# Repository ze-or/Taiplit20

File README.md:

# Taiplit20
20 key wireless split ergonomic keyboard

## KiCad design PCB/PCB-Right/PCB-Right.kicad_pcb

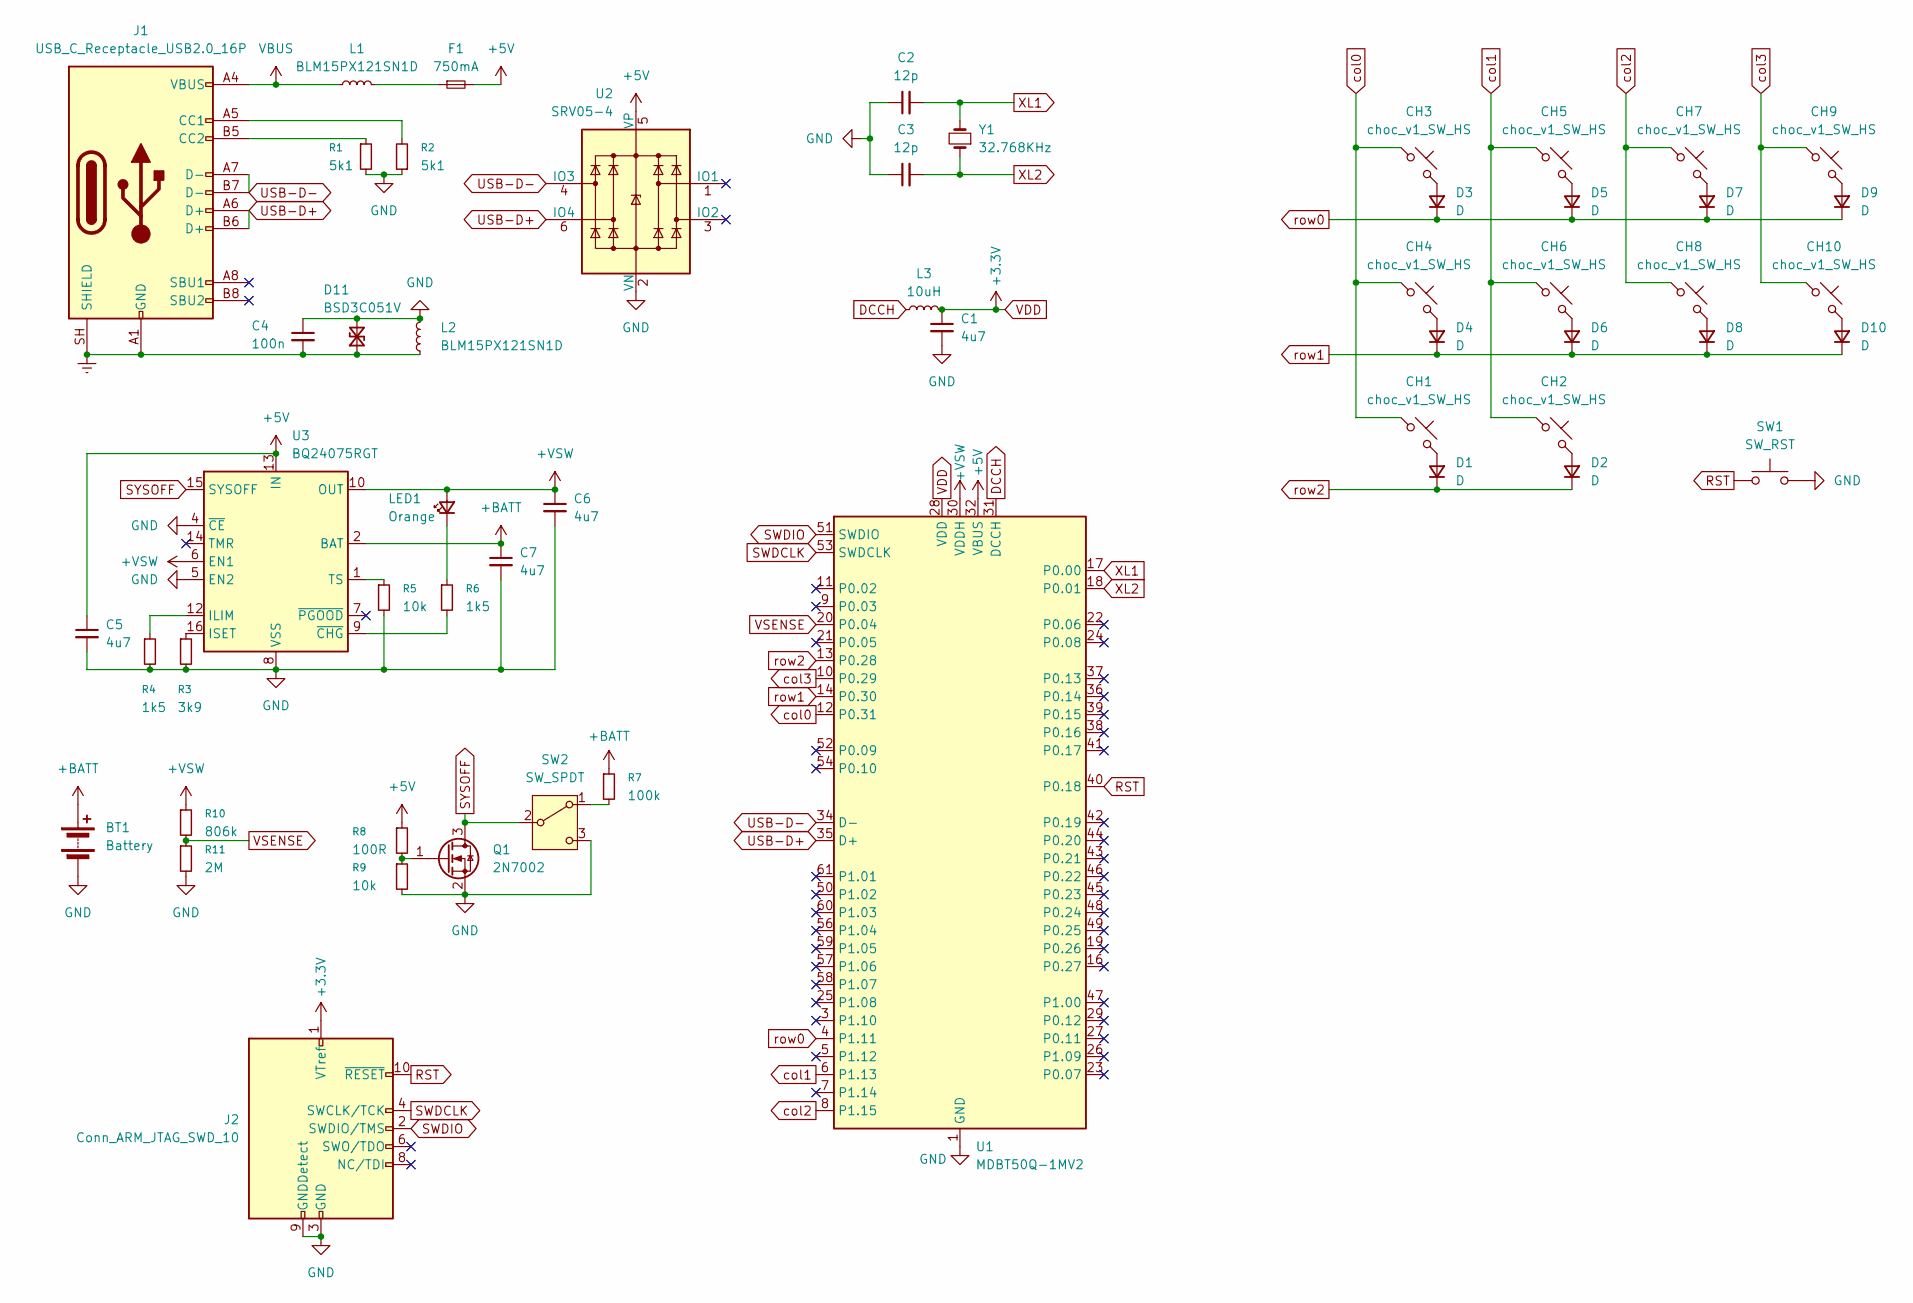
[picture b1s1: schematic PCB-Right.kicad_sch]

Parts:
BT1: Battery; JST_ACH_BM02B-ACHSS-GAN-ETF_1x02-1MP_P1.20mm_Vertical
C1, C5, C6, C7: 4u7; C_0603_1608Metric
C2, C3: 12p; C_0603_1608Metric
C4: 100n; C_0603_1608Metric
CH1, CH2, CH3, CH4, CH5, CH6, CH7, CH8, CH9, CH10: choc_v1_SW_HS; SW_choc_v2_HS_CPG135001S30_1u
D1, D2, D3, D4, D5, D6, D7, D8, D9, D10: D; D_SOD-123
D11: BSD3C051V; D_SOD-323
F1: 750mA; Fuse_1206_3216Metric
J1: USB_C_Receptacle_USB2.0_16P; USB_C_Receptacle_HRO_TYPE-C-31-M-12
J2: Conn_ARM_JTAG_SWD_10; PinHeader_2x05_P1.27mm_Vertical
L1, L2: BLM15PX121SN1D; L_0402_1005Metric
L3: 10uH; L_0603_1608Metric
LED1: Orange; LED_0805_2012Metric
Q1: 2N7002; SOT-23
R1, R2: 5k1; R_0603_1608Metric
R3: 3k9; R_0603_1608Metric
R4, R6: 1k5; R_0603_1608Metric
R5, R9: 10k; R_0603_1608Metric
R7: 100k; R_0603_1608Metric
R8: 100R; R_0603_1608Metric
R10: 806k; R_0603_1608Metric
R11: 2M; R_0603_1608Metric
SW1: SW_RST; SW_SPST_TL3342
SW2: SW_SPDT; SW_MSK12C02-HB
U1: MDBT50Q-1MV2; Raytac_MDBT50Q
U2: SRV05-4; SOT-23-6
U3: BQ24075RGT; VQFN-16-1EP_3x3mm_P0.5mm_EP1.6x1.6mm
Y1: 32.768KHz; Crystal_SMD_3215-2Pin_3.2x1.5mm

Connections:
+5V: C5.1, F1.2, R8.1, U1.32 (VBUS), U2.5 (VP), U3.13 (IN)
+BATT: BT1.1 (+), C7.1, R7.1, U3.2 (BAT), U3.3 (BAT)
+VSW: C6.1, LED1.2 (A), R10.1, U1.30 (VDDH), U3.6 (EN1), U3.10 (OUT), U3.11 (OUT)
DCCH: L3.1, U1.31 (DCCH)
Earth: C4.2, D11.1 (A1), J1.A1 (GND), J1.A12 (GND), J1.B1 (GND), J1.B12 (GND), J1.SH (SHIELD), L2.1
GND: BT1.2 (-), C1.2, C2.1, C3.1, C4.1, C5.2, C6.2, C7.2, D11.2 (A2), J2.3 (GND), J2.5 (GND), J2.9 (GNDDetect), L2.2, Q1.2 (S), R1.2, R2.1, R3.2, R4.2, R5.2, R9.2, R11.2, SW1.2, SW2.3 (C), U1.1 (GND), U1.2 (GND), U1.15 (GND), U1.33 (GND), U1.55 (GND), U2.2 (VN), U3.4 (~CE), U3.5 (EN2), U3.8 (VSS), U3.17 (VSS)
unnamed: CH1.2, D1.2 (A)
unnamed: CH2.2, D2.2 (A)
unnamed: CH3.2, D3.2 (A)
unnamed: CH4.2, D4.2 (A)
unnamed: CH5.2, D5.2 (A)
unnamed: CH6.2, D6.2 (A)
unnamed: CH7.2, D7.2 (A)
unnamed: CH8.2, D8.2 (A)
unnamed: CH9.2, D9.2 (A)
unnamed: CH10.2, D10.2 (A)
unnamed: F1.1, L1.2
unnamed: J1.A5 (CC1), R2.2
unnamed: J1.B5 (CC2), R1.1
unnamed: LED1.1 (K), R6.1
unnamed: Q1.1 (G), R8.2, R9.1
unnamed: R7.2, SW2.1 (A)
unnamed: R4.1, U3.12 (ILIM)
unnamed: R3.1, U3.16 (ISET)
unnamed: R5.1, U3.1 (TS)
unnamed: R6.2, U3.9 (~CHG)
RST: J2.10 (~RESET), SW1.1, U1.40 (P0.18)
SWDCLK: J2.4 (SWCLK/TCK), U1.53 (SWDCLK)
SWDIO: J2.2 (SWDIO/TMS), U1.51 (SWDIO)
SYSOFF: Q1.3 (D), SW2.2 (B), U3.15 (SYSOFF)
USB-D+: J1.A6 (D+), J1.B6 (D+), U1.35 (D+), U2.6 (IO4)
USB-D-: J1.A7 (D-), J1.B7 (D-), U1.34 (D-), U2.4 (IO3)
VBUS: J1.A4 (VBUS), J1.A9 (VBUS), J1.B4 (VBUS), J1.B9 (VBUS), L1.1
VDD: C1.1, J2.1 (VTref), L3.2, U1.28 (VDD)
VSENSE: R10.2, R11.1, U1.20 (P0.04)
XL1: C2.2, U1.17 (P0.00), Y1.2
XL2: C3.2, U1.18 (P0.01), Y1.1
col0: CH1.1, CH3.1, CH4.1, U1.12 (P0.31)
col1: CH2.1, CH5.1, CH6.1, U1.6 (P1.13)
col2: CH7.1, CH8.1, U1.8 (P1.15)
col3: CH9.1, CH10.1, U1.10 (P0.29)
row0: D3.1 (K), D5.1 (K), D7.1 (K), D9.1 (K), U1.4 (P1.11)
row1: D4.1 (K), D6.1 (K), D8.1 (K), D10.1 (K), U1.14 (P0.30)
row2: D1.1 (K), D2.1 (K), U1.13 (P0.28)

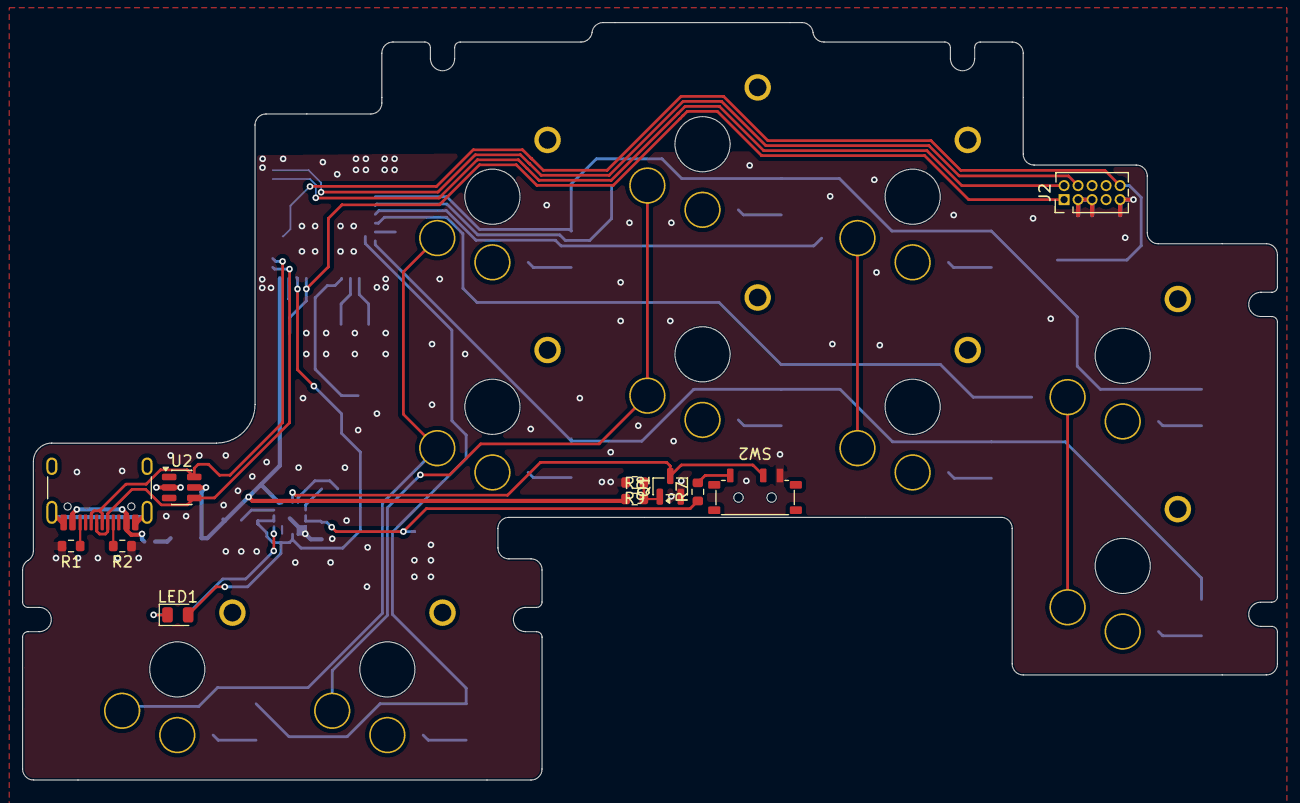
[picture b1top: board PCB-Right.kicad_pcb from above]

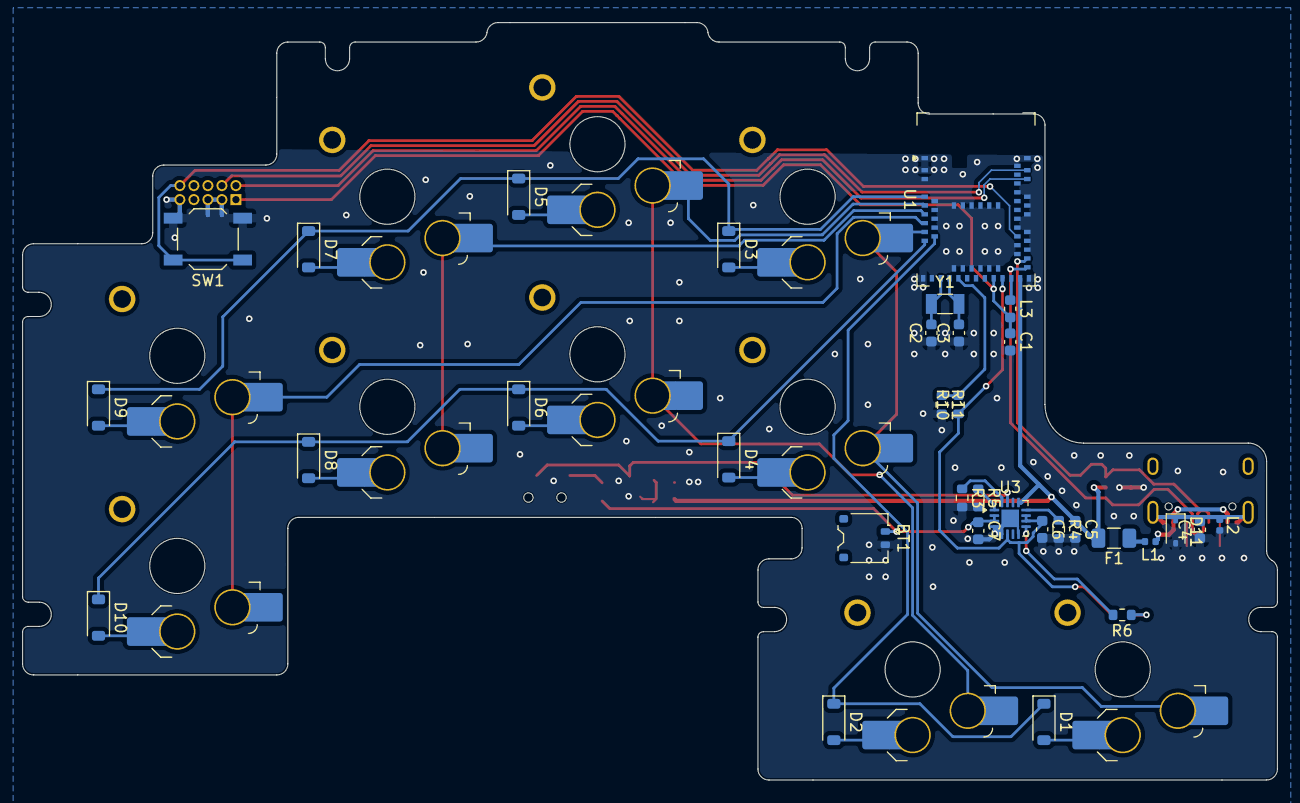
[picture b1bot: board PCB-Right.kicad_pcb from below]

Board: 2 copper layers, 113.8 x 68.7 mm, 54 parts (43 on the bottom side), 44 nets.
